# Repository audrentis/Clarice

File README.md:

# Clarice-F103

## About
An Alice layout PCB based on Yuktsi's files

### PCB Features
* Bottom mount USB Type-C 
* Uses STM32F103 MCU
* Support for in-switch LEDs 
* 3 indicator lights in original positions 
* Rotary Encoder footprint at top of macro cluster
* Markings on F.Cu and B.Silks for different switch and stabilizer positions

Uses [xyzz's STM32F103 Bootloader](https://github.com/xyzz/stm32f103-keyboard-bootloader)

### Supported Layouts

In the production folder is the files for pcb production from JLCPCB and the raw files for an acrylic case (3mm acrylic layers, 1.5mm switch plate [both half and full plates included])
Doc folder contains firmware 
# Disclaimer
**As stated in the license, I provide these designs as-is and as-available and provide no warranty or guarantees of functionality**  
this is untested and a work in progress. Use these files at your own risk.

# License 
<br />This work is licensed under a <a rel="license" 
href="http://creativecommons.org/licenses/by-nc-sa/4.0/">Creative Commons Attribution-NonCommercial-ShareAlike 4.0 International License</a>.

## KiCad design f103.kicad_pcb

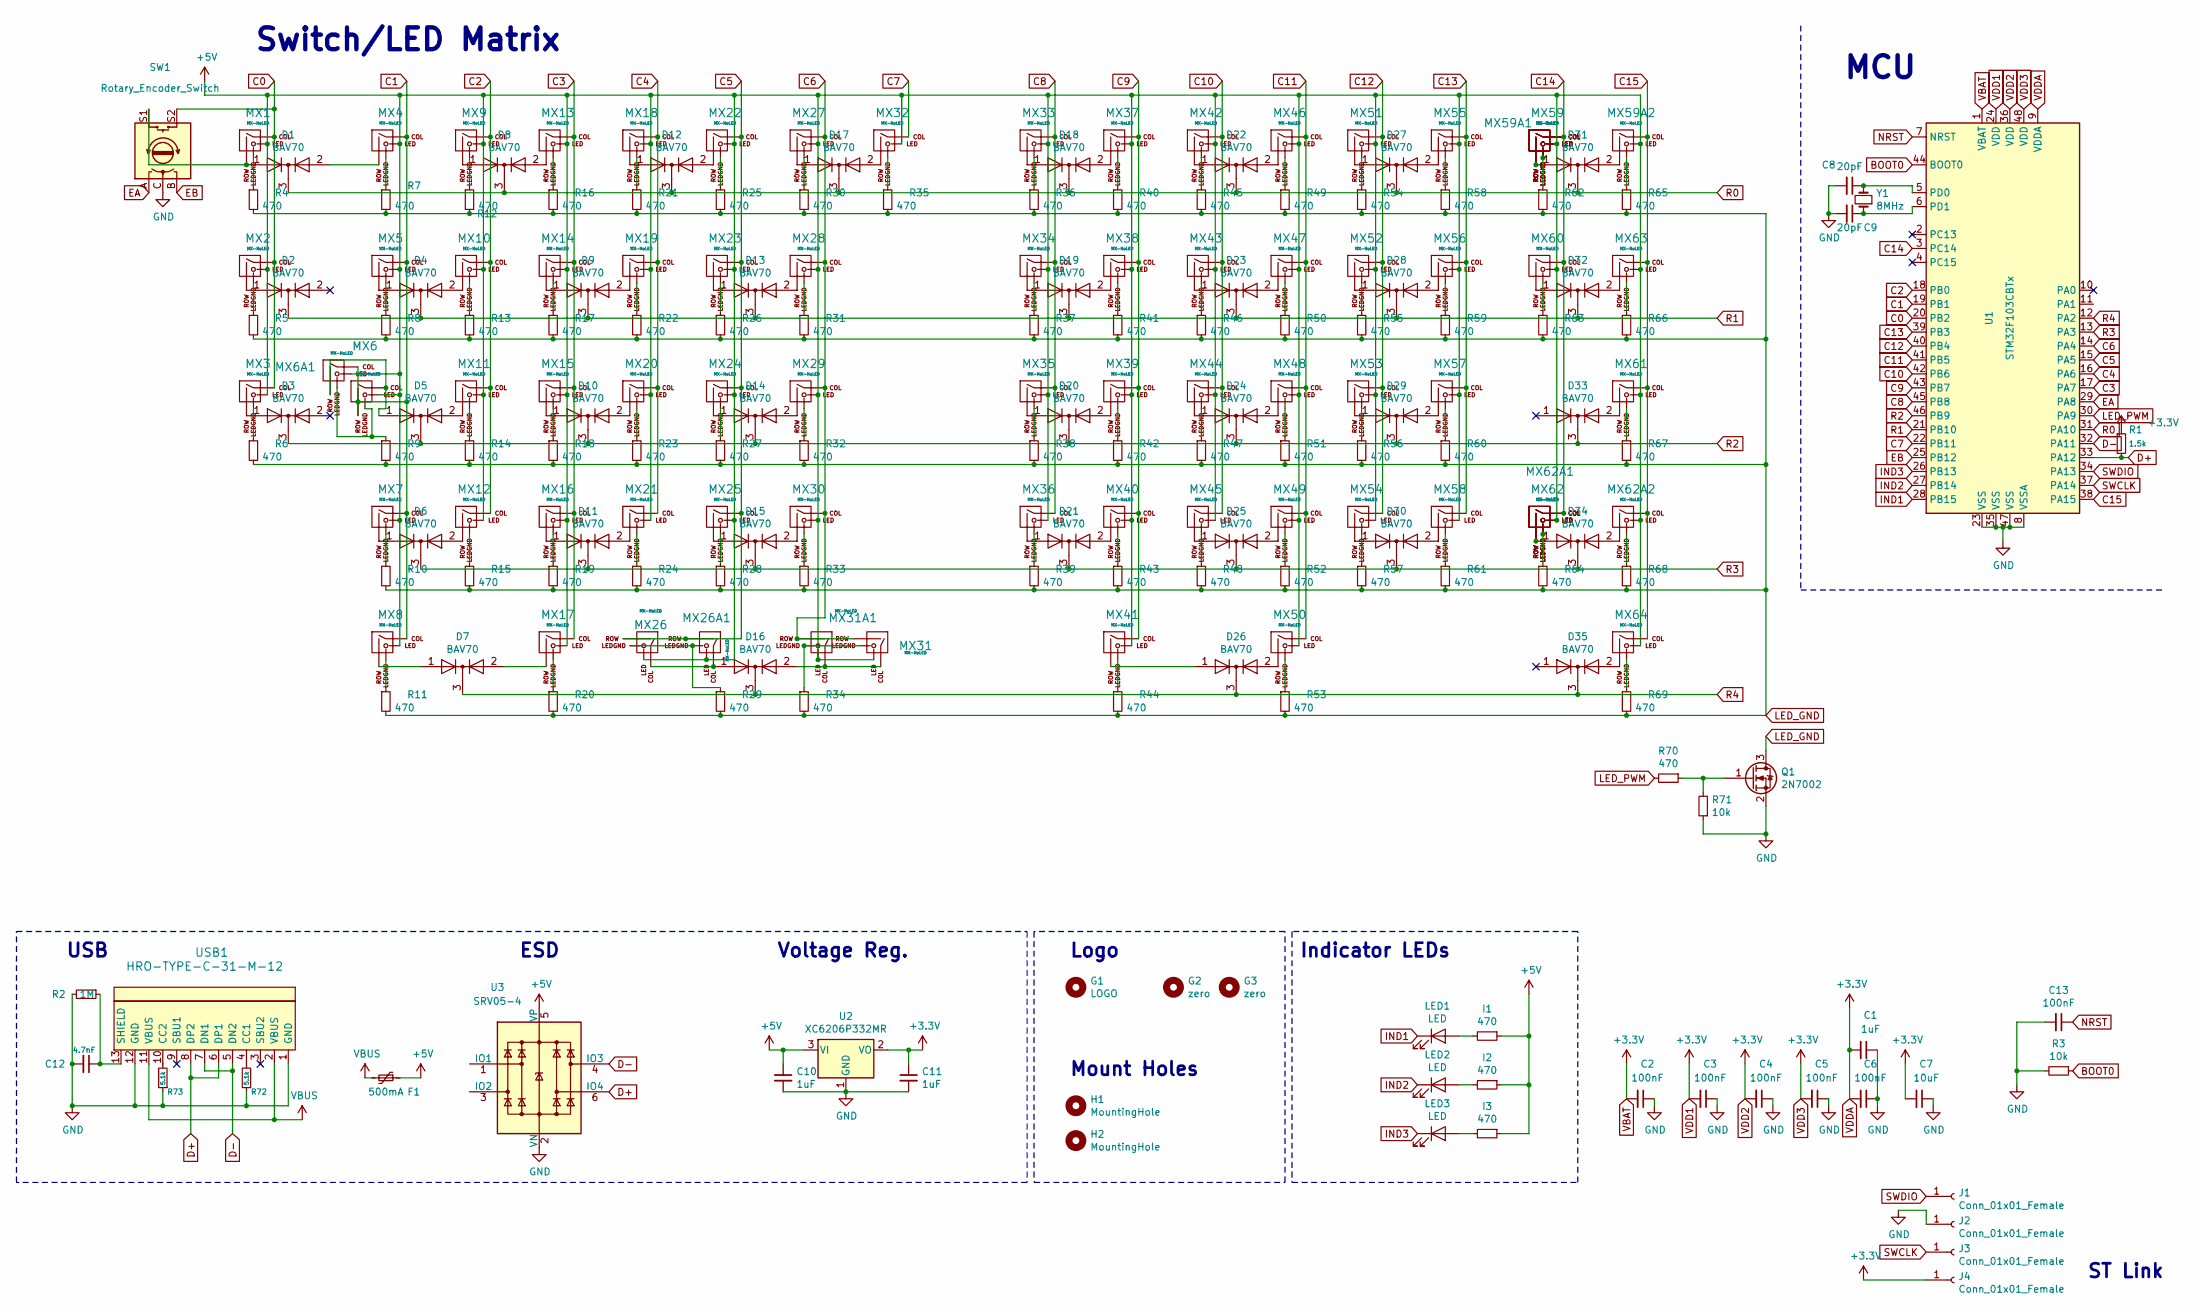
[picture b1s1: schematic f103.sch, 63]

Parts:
C1, C10, C11: 1uF; C_0603_1608Metric
C2, C3, C4, C5, C6, C13: 100nF; C_0603_1608Metric
C7: 10uF; C_0603_1608Metric
C8, C9: 20pF; C_0603_1608Metric
C12: 4.7nF; C_0603_1608Metric
D1: BAV70; SOT-23; LCSC C68978
D2, D3, D4, D5, D6, D7, D8, D9, D10, D11, D12, D13, D14, D15, D16, D17, D18, D19, D20, D21, D22, D23, D24, D25, D26, D27, D28, D29, D30, D31, D32, D33, D34, D35: BAV70; SOT-23
F1: 500mA; Fuse_1206_3216Metric; Part # C369159
G1: LOGO; Clarice_logo
G2, G3: zero; 0222
H1, H2: MountingHole; MountingHole_5mm
I1, I2, I3: 470; R_0603_1608Metric
J1, J2, J3, J4: Conn_01x01_Female; TestPoint_Pad_D1.5mm
LED1, LED2, LED3: LED; LED_D3.0mm
MX1, MX2, MX3, MX4, MX9, MX10, MX11, MX12, MX13, MX14, MX15, MX16, MX18, MX19, MX20, MX21, MX22, MX23, MX24, MX25, MX27, MX28, MX29, MX30, MX31, MX32, MX33, MX34, MX35, MX36, MX37, MX38, MX39, MX40, MX42, MX43, MX44, MX45, MX46, MX47, MX48, MX49, MX51, MX52, MX53, MX54, MX55, MX56, MX57, MX58, MX59A1, MX59A2, MX60, MX62A2: MX-NoLED; MXOnly-1U
MX5, MX8, MX17, MX50, MX63, MX64: MX-NoLED; MXOnly-1.5U
MX6, MX62A1: MX-NoLED; MXOnly-1.75U
MX6A1, MX31A1: MX-NoLED; MXOnly-1.25U
MX7: MX-NoLED; MXOnly-2.25U
MX26, MX61: MX-NoLED; MXOnly-2.25U-ReversedStabilizers
MX26A1: MX-NoLED; MXOnly-2U-ReversedStabilizers
MX41: MX-NoLED; MXOnly-2.75U-ReversedStabilizers
MX59: MX-NoLED; MXOnly-2U
MX62: MX-NoLED; MXOnly-2.75U
Q1: 2N7002; SOT-23
R1: 1.5k; R_0603_1608Metric
R2: 1M; R_0603_1608Metric
R3, R71: 10k; R_0603_1608Metric
R4: 470; R_0603_1608Metric; LCSC C23179
R5, R6, R7, R8, R9, R10, R11, R12, R13, R14, R15, R16, R17, R18, R19, R20, R21, R22, R23, R24, R25, R26, R27, R28, R29, R30, R31, R32, R33, R34, R35, R36, R37, R38, R39, R40, R41, R42, R43, R44, R45, R46, R47, R48, R49, R50, R51, R52, R53, R54, R55, R56, R57, R58, R59, R60, R61, R62, R63, R64, R65, R66, R67, R68, R69, R70: 470; R_0603_1608Metric
R72, R73: 5.1k; R_0603_1608Metric
SW1: Rotary_Encoder_Switch; RotaryEncoder_Alps_EC11E-Switch_Vertical_H20mm
U1: STM32F103CBTx; LQFP-48_7x7mm_P0.5mm; Part # C8734
U2: XC6206P332MR; SOT-23; Part # C5446
U3: SRV05-4; SOT-23-6; Part # C85364
USB1: HRO-TYPE-C-31-M-12; HRO-TYPE-C-31-M-12-jlc
Y1: 8MHz; Crystal_SMD_5032-2Pin_5.0x3.2mm; Part # C115962

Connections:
+5V: C10.1, F1.1, I1.1, I2.1, I3.1, MX1.3 (LED), MX2.3 (LED), MX3.3 (LED), MX4.3 (LED), MX5.3 (LED), MX6.3 (LED), MX6A1.3 (LED), MX7.3 (LED), MX8.3 (LED), MX9.3 (LED), MX10.3 (LED), MX11.3 (LED), MX12.3 (LED), MX13.3 (LED), MX14.3 (LED), MX15.3 (LED), MX16.3 (LED), MX17.3 (LED), MX18.3 (LED), MX19.3 (LED), MX20.3 (LED), MX21.3 (LED), MX22.3 (LED), MX23.3 (LED), MX24.3 (LED), MX25.3 (LED), MX26.3 (LED), MX26A1.3 (LED), MX27.3 (LED), MX28.3 (LED), MX29.3 (LED), MX30.3 (LED), MX31.3 (LED), MX31A1.3 (LED), MX32.3 (LED), MX33.3 (LED), MX34.3 (LED), MX35.3 (LED), MX36.3 (LED), MX37.3 (LED), MX38.3 (LED), MX39.3 (LED), MX40.3 (LED), MX41.3 (LED), MX42.3 (LED), MX43.3 (LED), MX44.3 (LED), MX45.3 (LED), MX46.3 (LED), MX47.3 (LED), MX48.3 (LED), MX49.3 (LED), MX50.3 (LED), MX51.3 (LED), MX52.3 (LED), MX53.3 (LED), MX54.3 (LED), MX55.3 (LED), MX56.3 (LED), MX57.3 (LED), MX58.3 (LED), MX59.3 (LED), MX59A1.3 (LED), MX59A2.3 (LED), MX60.3 (LED), MX61.3 (LED), MX62.3 (LED), MX62A1.3 (LED), MX62A2.3 (LED), MX63.3 (LED), MX64.3 (LED), U2.3 (VI), U3.5 (VP)
BOOT0: R3.1, U1.44 (BOOT0)
C0: MX1.1 (COL), MX2.1 (COL), MX3.1 (COL), SW1.S2, U1.20 (PB2)
C1: MX4.1 (COL), MX5.1 (COL), MX6.2 (ROW), MX6A1.1 (COL), MX7.1 (COL), MX8.1 (COL), U1.19 (PB1)
C2: MX9.1 (COL), MX10.1 (COL), MX11.1 (COL), MX12.1 (COL), U1.18 (PB0)
C3: MX13.1 (COL), MX14.1 (COL), MX15.1 (COL), MX16.1 (COL), MX17.1 (COL), U1.17 (PA7)
C4: MX18.1 (COL), MX19.1 (COL), MX20.1 (COL), MX21.1 (COL), U1.16 (PA6)
C5: MX22.1 (COL), MX23.1 (COL), MX24.1 (COL), MX25.1 (COL), MX26.2 (ROW), MX26A1.2 (ROW), U1.15 (PA5)
C6: MX27.1 (COL), MX28.1 (COL), MX29.1 (COL), MX30.1 (COL), MX31.2 (ROW), MX31A1.2 (ROW), U1.14 (PA4)
C7: MX32.1 (COL), U1.22 (PB11)
C8: MX33.1 (COL), MX34.1 (COL), MX35.1 (COL), MX36.1 (COL), U1.45 (PB8)
C9: MX37.1 (COL), MX38.1 (COL), MX39.1 (COL), MX40.1 (COL), MX41.1 (COL), U1.43 (PB7)
C10: MX42.1 (COL), MX43.1 (COL), MX44.1 (COL), MX45.1 (COL), U1.42 (PB6)
C11: MX46.1 (COL), MX47.1 (COL), MX48.1 (COL), MX49.1 (COL), MX50.1 (COL), U1.41 (PB5)
C12: MX51.1 (COL), MX52.1 (COL), MX53.1 (COL), MX54.1 (COL), U1.40 (PB4)
C13: MX55.1 (COL), MX56.1 (COL), MX57.1 (COL), MX58.1 (COL), U1.39 (PB3)
C14: MX59.1 (COL), MX59A1.1 (COL), MX60.1 (COL), MX62.1 (COL), MX62A1.1 (COL), U1.3 (PC14)
C15: MX59A2.1 (COL), MX61.1 (COL), MX62A2.1 (COL), MX63.1 (COL), MX64.1 (COL), U1.38 (PA15)
D+: R1.2, U1.33 (PA12), U3.6 (IO4), USB1.6 (DP1), USB1.8 (DP2)
D-: U1.32 (PA11), U3.4 (IO3), USB1.5 (DN2), USB1.7 (DN1)
EA: SW1.A, U1.29 (PA8)
EB: SW1.B, U1.25 (PB12)
GND: C1.1, C2.1, C3.1, C4.1, C5.1, C6.1, C7.1, C8.2, C9.2, C10.2, C11.2, C12.2, C13.2, J2.1, Q1.2 (S), R2.2, R3.2, R71.1, R72.1, R73.1, SW1.C, U1.8 (VSSA), U1.23 (VSS), U1.35 (VSS), U1.47 (VSS), U2.1 (GND), U3.2 (VN), USB1.1 (GND), USB1.12 (GND)
IND1: LED1.1 (K), U1.28 (PB15)
IND2: LED2.1 (K), U1.27 (PB14)
IND3: LED3.1 (K), U1.26 (PB13)
LED_GND: Q1.3 (D), R4.2, R5.2, R6.2, R7.2, R8.2, R9.2, R10.2, R11.2, R12.2, R13.2, R14.2, R15.2, R16.2, R17.2, R18.2, R19.2, R20.2, R21.2, R22.2, R23.2, R24.2, R25.2, R26.2, R27.2, R28.2, R29.2, R30.2, R31.2, R32.2, R33.2, R34.2, R35.2, R36.2, R37.2, R38.2, R39.2, R40.2, R41.2, R42.2, R43.2, R44.2, R45.2, R46.2, R47.2, R48.2, R49.2, R50.2, R51.2, R52.2, R53.2, R54.2, R55.2, R56.2, R57.2, R58.2, R59.2, R60.2, R61.2, R62.2, R63.2, R64.2, R65.2, R66.2, R67.2, R68.2, R69.2
LED_PWM: R70.2, U1.30 (PA9)
NRST: C13.1, U1.7 (NRST)
unnamed: C8.1, U1.5 (PD0), Y1.2
unnamed: C9.1, U1.6 (PD1), Y1.1
unnamed: C12.1, R2.1, USB1.13 (SHIELD)
unnamed: D1.1 (A), MX1.2 (ROW), SW1.S1
unnamed: D1.2 (A), MX4.2 (ROW)
unnamed: D2.1 (A), MX2.2 (ROW)
unnamed: D3.1 (A), MX3.2 (ROW)
unnamed: D4.1 (A), MX5.2 (ROW)
unnamed: D4.2 (A), MX10.2 (ROW)
unnamed: D5.1 (A), MX6.1 (COL), MX6A1.2 (ROW)
unnamed: D5.2 (A), MX11.2 (ROW)
unnamed: D6.1 (A), MX7.2 (ROW)
unnamed: D6.2 (A), MX12.2 (ROW)
unnamed: D7.1 (A), MX8.2 (ROW)
unnamed: D7.2 (A), MX17.2 (ROW)
unnamed: D8.1 (A), MX9.2 (ROW)
unnamed: D8.2 (A), MX13.2 (ROW)
unnamed: D9.1 (A), MX14.2 (ROW)
unnamed: D9.2 (A), MX19.2 (ROW)
unnamed: D10.1 (A), MX15.2 (ROW)
unnamed: D10.2 (A), MX20.2 (ROW)
unnamed: D11.1 (A), MX16.2 (ROW)
unnamed: D11.2 (A), MX21.2 (ROW)
unnamed: D12.1 (A), MX18.2 (ROW)
unnamed: D12.2 (A), MX22.2 (ROW)
unnamed: D13.1 (A), MX23.2 (ROW)
unnamed: D13.2 (A), MX28.2 (ROW)
unnamed: D14.1 (A), MX24.2 (ROW)
unnamed: D14.2 (A), MX29.2 (ROW)
unnamed: D15.1 (A), MX25.2 (ROW)
unnamed: D15.2 (A), MX30.2 (ROW)
unnamed: D16.1 (A), MX26.1 (COL), MX26A1.1 (COL)
unnamed: D16.2 (A), MX31.1 (COL), MX31A1.1 (COL)
unnamed: D17.1 (A), MX27.2 (ROW)
unnamed: D17.2 (A), MX32.2 (ROW)
unnamed: D18.1 (A), MX33.2 (ROW)
unnamed: D18.2 (A), MX37.2 (ROW)
unnamed: D19.1 (A), MX34.2 (ROW)
unnamed: D19.2 (A), MX38.2 (ROW)
unnamed: D20.1 (A), MX35.2 (ROW)
unnamed: D20.2 (A), MX39.2 (ROW)
unnamed: D21.1 (A), MX36.2 (ROW)
unnamed: D21.2 (A), MX40.2 (ROW)
unnamed: D22.1 (A), MX42.2 (ROW)
unnamed: D22.2 (A), MX46.2 (ROW)
unnamed: D23.1 (A), MX43.2 (ROW)
unnamed: D23.2 (A), MX47.2 (ROW)
unnamed: D24.1 (A), MX44.2 (ROW)
unnamed: D24.2 (A), MX48.2 (ROW)
unnamed: D25.1 (A), MX45.2 (ROW)
unnamed: D25.2 (A), MX49.2 (ROW)
unnamed: D26.1 (A), MX41.2 (ROW)
unnamed: D26.2 (A), MX50.2 (ROW)
unnamed: D27.1 (A), MX51.2 (ROW)
unnamed: D27.2 (A), MX55.2 (ROW)
unnamed: D28.1 (A), MX52.2 (ROW)
unnamed: D28.2 (A), MX56.2 (ROW)
unnamed: D29.1 (A), MX53.2 (ROW)
unnamed: D29.2 (A), MX57.2 (ROW)
unnamed: D30.1 (A), MX54.2 (ROW)
unnamed: D30.2 (A), MX58.2 (ROW)
unnamed: D31.1 (A), MX59.2 (ROW), MX59A1.2 (ROW)
unnamed: D31.2 (A), MX59A2.2 (ROW)
unnamed: D32.1 (A), MX60.2 (ROW)
unnamed: D32.2 (A), MX63.2 (ROW)
unnamed: D33.2 (A), MX61.2 (ROW)
unnamed: D34.1 (A), MX62.2 (ROW), MX62A1.2 (ROW)
unnamed: D34.2 (A), MX62A2.2 (ROW)
unnamed: D35.2 (A), MX64.2 (ROW)
unnamed: I1.2, LED1.2 (A)
unnamed: I2.2, LED2.2 (A)
unnamed: I3.2, LED3.2 (A)
unnamed: MX1.4 (LEDGND), R4.1
unnamed: MX2.4 (LEDGND), R5.1
unnamed: MX3.4 (LEDGND), R6.1
unnamed: MX4.4 (LEDGND), R7.1
unnamed: MX5.4 (LEDGND), R8.1
unnamed: MX6.4 (LEDGND), MX6A1.4 (LEDGND), R9.1
unnamed: MX7.4 (LEDGND), R10.1
unnamed: MX8.4 (LEDGND), R11.1
unnamed: MX9.4 (LEDGND), R12.1
unnamed: MX10.4 (LEDGND), R13.1
unnamed: MX11.4 (LEDGND), R14.1
unnamed: MX12.4 (LEDGND), R15.1
unnamed: MX13.4 (LEDGND), R16.1
unnamed: MX14.4 (LEDGND), R17.1
unnamed: MX15.4 (LEDGND), R18.1
unnamed: MX16.4 (LEDGND), R19.1
unnamed: MX17.4 (LEDGND), R20.1
unnamed: MX18.4 (LEDGND), R21.1
unnamed: MX19.4 (LEDGND), R22.1
unnamed: MX20.4 (LEDGND), R23.1
unnamed: MX21.4 (LEDGND), R24.1
unnamed: MX22.4 (LEDGND), R25.1
unnamed: MX23.4 (LEDGND), R26.1
unnamed: MX24.4 (LEDGND), R27.1
unnamed: MX25.4 (LEDGND), R28.1
unnamed: MX26.4 (LEDGND), MX26A1.4 (LEDGND), R29.1
unnamed: MX27.4 (LEDGND), R30.1
unnamed: MX28.4 (LEDGND), R31.1
unnamed: MX29.4 (LEDGND), R32.1
unnamed: MX30.4 (LEDGND), R33.1
unnamed: MX31.4 (LEDGND), MX31A1.4 (LEDGND), R34.1
unnamed: MX32.4 (LEDGND), R35.1
unnamed: MX33.4 (LEDGND), R36.1
unnamed: MX34.4 (LEDGND), R37.1
unnamed: MX35.4 (LEDGND), R38.1
unnamed: MX36.4 (LEDGND), R39.1
unnamed: MX37.4 (LEDGND), R40.1
unnamed: MX38.4 (LEDGND), R41.1
unnamed: MX39.4 (LEDGND), R42.1
unnamed: MX40.4 (LEDGND), R43.1
unnamed: MX41.4 (LEDGND), R44.1
unnamed: MX42.4 (LEDGND), R45.1
unnamed: MX43.4 (LEDGND), R46.1
unnamed: MX44.4 (LEDGND), R47.1
unnamed: MX45.4 (LEDGND), R48.1
unnamed: MX46.4 (LEDGND), R49.1
unnamed: MX47.4 (LEDGND), R50.1
unnamed: MX48.4 (LEDGND), R51.1
unnamed: MX49.4 (LEDGND), R52.1
unnamed: MX50.4 (LEDGND), R53.1
unnamed: MX51.4 (LEDGND), R54.1
unnamed: MX52.4 (LEDGND), R55.1
unnamed: MX53.4 (LEDGND), R56.1
unnamed: MX54.4 (LEDGND), R57.1
unnamed: MX55.4 (LEDGND), R58.1
unnamed: MX56.4 (LEDGND), R59.1
unnamed: MX57.4 (LEDGND), R60.1
unnamed: MX58.4 (LEDGND), R61.1
unnamed: MX59.4 (LEDGND), MX59A1.4 (LEDGND), R62.1
unnamed: MX59A2.4 (LEDGND), R65.1
unnamed: MX60.4 (LEDGND), R63.1
unnamed: MX61.4 (LEDGND), R67.1
unnamed: MX62.4 (LEDGND), MX62A1.4 (LEDGND), R64.1
unnamed: MX62A2.4 (LEDGND), R68.1
unnamed: MX63.4 (LEDGND), R66.1
unnamed: MX64.4 (LEDGND), R69.1
unnamed: Q1.1 (G), R70.1, R71.2
unnamed: R72.2, USB1.4 (CC1)
unnamed: R73.2, USB1.10 (CC2)
R0: D1.3 (K), D8.3 (K), D12.3 (K), D17.3 (K), D18.3 (K), D22.3 (K), D27.3 (K), D31.3 (K), U1.31 (PA10)
R1: D2.3 (K), D4.3 (K), D9.3 (K), D13.3 (K), D19.3 (K), D23.3 (K), D28.3 (K), D32.3 (K), U1.21 (PB10)
R2: D3.3 (K), D5.3 (K), D10.3 (K), D14.3 (K), D20.3 (K), D24.3 (K), D29.3 (K), D33.3 (K), U1.46 (PB9)
R3: D6.3 (K), D11.3 (K), D15.3 (K), D21.3 (K), D25.3 (K), D30.3 (K), D34.3 (K), U1.13 (PA3)
R4: D7.3 (K), D16.3 (K), D26.3 (K), D35.3 (K), U1.12 (PA2)
SWCLK: J3.1, U1.37 (PA14)
SWDIO: J1.1, U1.34 (PA13)
VBAT: C1.2, C2.2, C3.2, C4.2, C5.2, C6.2, C7.2, C11.1, J4.1, R1.1, U1.1 (VBAT), U1.9 (VDDA), U1.24 (VDD), U1.36 (VDD), U1.48 (VDD), U2.2 (VO)
VBUS: F1.2, USB1.2 (VBUS), USB1.11 (VBUS)

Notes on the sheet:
Switch/LED Matrix
MCU
ST Link
USB
Voltage Reg.
ESD
Logo
Mount Holes
Indicator LEDs

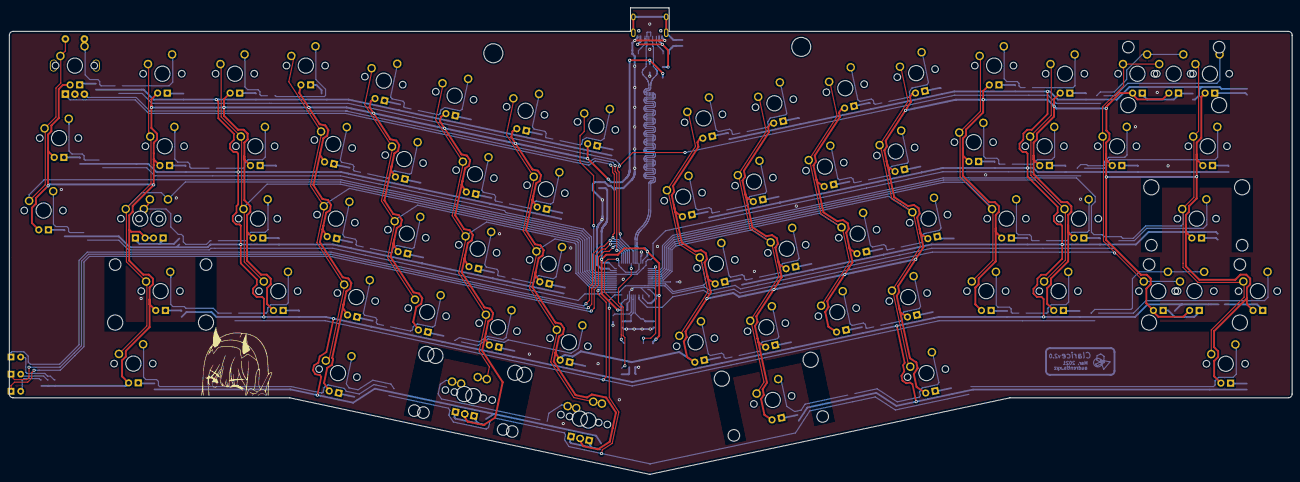
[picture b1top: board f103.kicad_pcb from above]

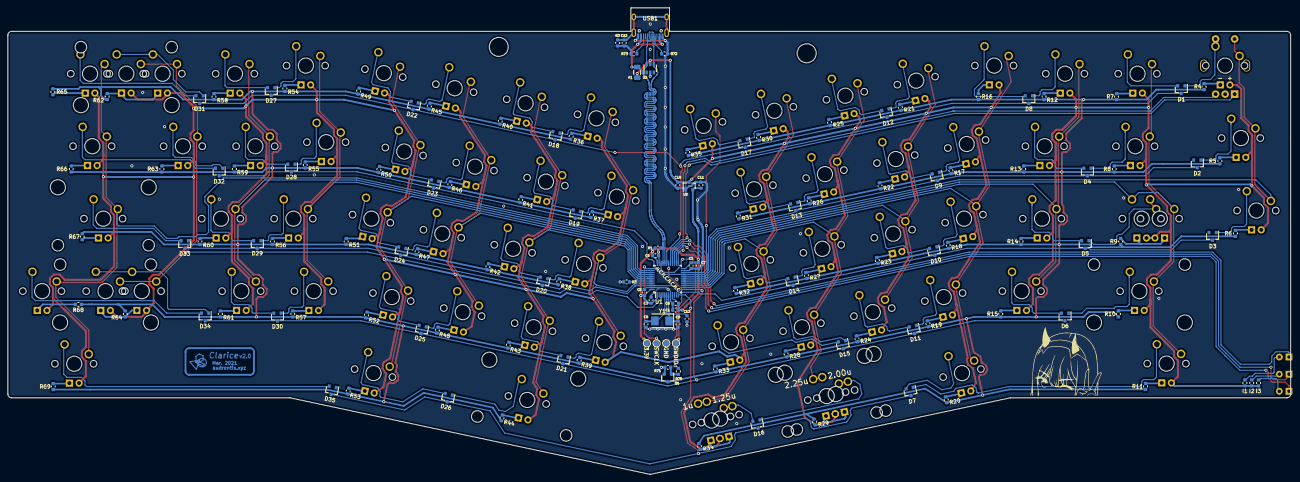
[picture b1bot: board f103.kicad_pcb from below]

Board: 2 copper layers, 337.2 x 122.6 mm, 215 parts (136 on the bottom side), 179 nets.

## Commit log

2021-01-20 Add submodules
2021-01-20 add proj
2021-01-20 fix libraries
2021-01-20 Add Production Files, Submit for review
2021-01-28 DRC I
2021-02-02 DRC II
    update silks and ground planes
2021-02-03 DRC III
    Switch to usb type-C
2021-02-08 DRC IV
2021-02-21 Checking Datasheet
2021-02-28 DRC Pass
2021-03-08 Finalizing
    - Firmware creation begun
    - add .step model of PCB
    - add gerbers, CPL, BOM
2021-03-31 overhaul: see description
    - remapped backlighting to A9
    - remapped encoder pad B to B12
    - updated ground fills
    - added 02 silkscreen
    - write firmware
    - add compiled binary file
2021-04-03 ordered prototypes
